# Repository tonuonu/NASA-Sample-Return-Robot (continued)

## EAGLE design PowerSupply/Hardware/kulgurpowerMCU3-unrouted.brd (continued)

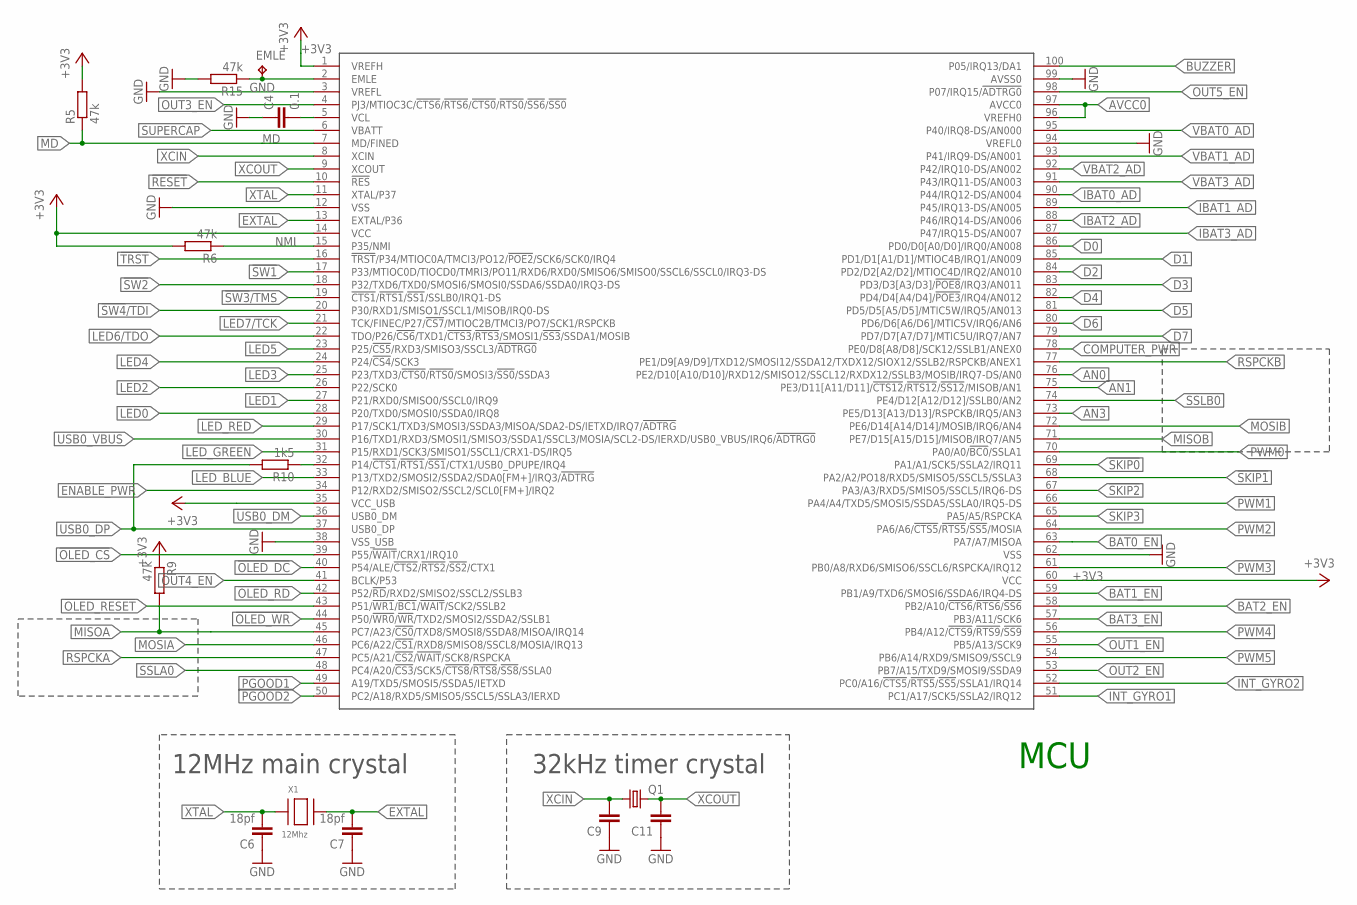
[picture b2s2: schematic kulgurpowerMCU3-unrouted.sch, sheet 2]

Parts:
C4: 0.1; 0603-CAP
C6, C7: 18pf; 0603-CAP
C9, C11: CAP0603-CAP; 0603-CAP
EMLE: TPB1,27; B1,27
Q1: CRYSTALMM20SS; MM20SS
R5, R6, R9, R15: 47k; R0603
R10: 1k5; R0603
U$14: R5F5630ADDFP; LTQFP100
X1: 12Mhz; NX5032

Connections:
!OLED_CS: U$14.39 (P55/!WAIT!/CRX1/IRQ10); also elsewhere on the board
!OLED_DC: U$14.40 (P54/ALE/!CTS2!/!RTS2!/!SS2!/CTX1); also elsewhere on the board
!OLED_RD: U$14.42 (P52/!RD!/RXD2/SMISO2/SSCL2/SSLB3); also elsewhere on the board
!OLED_RESET: U$14.43 (P51/!WR1!/!BC1!/!WAIT!/SCK2/SSLB2); also elsewhere on the board
!OLED_WR: U$14.44 (P50/!WR0!/!WR!/TXD2/SMOSI2/SSDA2/SSLB1); also elsewhere on the board
!RESET: U$14.10 (!RES!); also elsewhere on the board
!SKIP0: U$14.69 (PA1/A1/SCK5/SSLA2/IRQ11); also elsewhere on the board
!SKIP1: U$14.68 (PA2/A2/PO18/RXD5/SMISO5/SSCL5/SSLA3); also elsewhere on the board
!SKIP2: U$14.67 (PA3/A3/RXD5/SMISO5/SSCL5/IRQ6-DS); also elsewhere on the board
!SKIP3: U$14.65 (PA5/A5/RSPCKA); also elsewhere on the board
!SW1: U$14.17 (P33/MTIOC0D/TIOCD0/TMRI3/PO11/RXD6/RXD0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); also elsewhere on the board
!SW2: U$14.18 (P32/TXD6/TXD0/SMOSI6/SMOSI0/SSDA6/SSDA0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); also elsewhere on the board
!SW3!/TMS: U$14.19 (!CTS1!/!RTS1!/!SS1!/SSLB0/IRQ1-DS); also elsewhere on the board
!SW4!/TDI: U$14.20 (P30/RXD1/SMISO1/SSCL1/MISOB/IRQ0-DS); also elsewhere on the board
!TRST: U$14.16 (!TRST!/P34/MTIOC0A/TMCI3/PO12/!POE2!/SC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); also elsewhere on the board
+3V3: R5.2, R6.2, R9.1, U$14.1 (VREFH), U$14.14 (VCC), U$14.35 (VCC_USB), U$14.60 (VCC); also elsewhere on the board
AN0: U$14.76 (PE2/D10[A10/D10]/RXD12/SMISO12/SSCL12/R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); also elsewhere on the board
AN1: U$14.75 (PE3/D11[A11/D11]/!CTS12!/!RTS12!/!SS12!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); also elsewhere on the board
AN3: U$14.73 (PE5/D13[A13/D13]/RSPCKB/IRQ5/AN3); also elsewhere on the board
AVCC0: U$14.96 (VREFH0), U$14.97 (AVCC0); also elsewhere on the board
BAT0_EN: U$14.63 (PA7/A7/MISOA); also elsewhere on the board
BAT1_EN: U$14.59 (PB1/A9/TXD6/SMOSI6/SSDA6/IRQ4-DS); also elsewhere on the board
BAT2_EN: U$14.58 (PB2/A10/!CTS6!/!RTS6!/!SS6!); also elsewhere on the board
BAT3_EN: U$14.57 (PB3/A11/SCK6); also elsewhere on the board
BUZZER: U$14.100 (P05/IRQ13/DA1); also elsewhere on the board
COMPUTER_PWR: U$14.78 (PE0/D8[A8/D8]/SCK12/SSLB1/ANEX0); also elsewhere on the board
D0: U$14.86 (PD0/D0[A0/D0]/IRQ0/AN008); also elsewhere on the board
D1: U$14.85 (PD1/D1[A1/D1]/MTIOC4B/IRQ1/AN009); also elsewhere on the board
D2: U$14.84 (PD2/D2[A2/D2]/MTIOC4D/IRQ2/AN010); also elsewhere on the board
D3: U$14.83 (PD3/D3[A3/D3]/!POE8!/IRQ3/AN011); also elsewhere on the board
D4: U$14.82 (PD4/D4[A4/D4]/!POE3!/IRQ4/AN012); also elsewhere on the board
D5: U$14.81 (PD5/D5[A5/D5]/MTIC5W/IRQ5/AN013); also elsewhere on the board
D6: U$14.80 (PD6/D6[A6/D6]/MTIC5V/IRQ6/AN6); also elsewhere on the board
D7: U$14.79 (PD7/D7[A7/D7]/MTIC5U/IRQ7/AN7); also elsewhere on the board
EMLE: EMLE.TP, R15.1, U$14.2 (EMLE); also elsewhere on the board
ENABLE_PWR: U$14.34 (P12/RXD2/SMISO2/SSCL2/SCL0[FM+]/IRQ2); also elsewhere on the board
EXTAL: C7.2, U$14.13 (EXTAL/P36), X1.P$2
GND: C4.1, C6.1, C7.1, C9.1, C11.1, R15.2, U$14.3 (VREFL), U$14.12 (VSS), U$14.38 (VSS_USB), U$14.62 (VSS), U$14.94 (VREFL0), U$14.99 (AVSS0); also elsewhere on the board
IBAT0_AD: U$14.90 (P44/IRQ12-DS/AN004); also elsewhere on the board
IBAT1_AD: U$14.89 (P45/IRQ13-DS/AN005); also elsewhere on the board
IBAT2_AD: U$14.88 (P46/IRQ14-DS/AN006); also elsewhere on the board
IBAT3_AD: U$14.87 (P47/IRQ15-DS/AN007); also elsewhere on the board
INT_GYRO1: U$14.51 (PC1/A17/SCK5/SSLA2/IRQ12); also elsewhere on the board
INT_GYRO2: U$14.52 (PC0/A16/!CTS5!/!RTS5!/!SS5!/SSLA1/IRQ14); also elsewhere on the board
LED0: U$14.28 (P20/TXD0/SMOSI0/SSDA0/IRQ8); also elsewhere on the board
LED1: U$14.27 (P21/RXD0/SMISO0/SSCL0/IRQ9); also elsewhere on the board
LED2: U$14.26 (P22/SCK0); also elsewhere on the board
LED3: U$14.25 (P23/TXD3/!CTS0!/!RTS0!/SMOSI3/!SS0!/SSD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); also elsewhere on the board
LED4: U$14.24 (P24/!CS4!/SCK3); also elsewhere on the board
LED5: U$14.23 (P25/!CS5!/RXD3/SMISO3/SSCL3/!ADTRG0!); also elsewhere on the board
LED6/TDO: U$14.22 (TDO/P26/!CS6!/TXD1/!CTS3!/!RTS3!/SMOSI1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); also elsewhere on the board
LED7/TCK: U$14.21 (TCK/FINEC/P27/!CS7!/MTIOC2B/TMCI3/PO7/S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); also elsewhere on the board
LED_BLUE: U$14.33 (P13/TXD2/SMOSI2/SSDA2/SDA0[FM+]/IRQ3/!A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); also elsewhere on the board
LED_GREEN: U$14.31 (P15/RXD1/SCK3/SMISO1/SSCL1/CRX1-DS/IRQ5); also elsewhere on the board
LED_RED: U$14.29 (P17/SCK1/TXD3/SMOSI3/SSDA3/MISOA/SDA2-D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); also elsewhere on the board
MD: R5.1, U$14.7 (MD/FINED); also elsewhere on the board
MISOA: R9.2, U$14.45 (PC7/A23/!CS0!/TXD8/SMOSI8/SSDA8/MISOA/I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); also elsewhere on the board
MISOB: U$14.71 (PE7/D15[A15/D15]/MISOB/IRQ7/AN5); also elsewhere on the board
MOSIA: U$14.46 (PC6/A22/!CS1!/RXD8/SMISO8/SSCL8/MOSIA/I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); also elsewhere on the board
MOSIB: U$14.72 (PE6/D14[A14/D14]/MOSIB/IRQ6/AN4); also elsewhere on the board
unnamed: C4.2, U$14.5 (VCL)
NMI: R6.1, U$14.15 (P35/NMI)
OUT1_EN: U$14.55 (PB5/A13/SCK9); also elsewhere on the board
OUT2_EN: U$14.53 (PB7/A15/TXD9/SMOSI9/SSDA9); also elsewhere on the board
OUT3_EN: U$14.4 (PJ3/MTIOC3C/!CTS6!/!RTS6!/!CTS0!/!RTS0!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); also elsewhere on the board
OUT4_EN: U$14.41 (BCLK/P53); also elsewhere on the board
OUT5_EN: U$14.98 (P07/IRQ15/!ADTRG0); also elsewhere on the board
PGOOD1: U$14.49 (A19/TXD5/SMOSI5/SSDA5/IETXD); also elsewhere on the board
PGOOD2: U$14.50 (PC2/A18/RXD5/SMISO5/SSCL5/SSLA3/IERXD); also elsewhere on the board
PWM0: U$14.70 (PA0/A0/!BC0!/SSLA1); also elsewhere on the board
PWM1: U$14.66 (PA4/A4/TXD5/SMOSI5/SSDA5/SSLA0/IRQ5-DS); also elsewhere on the board
PWM2: U$14.64 (PA6/A6/!CTS5!/!RTS5!/!SS5!/MOSIA); also elsewhere on the board
PWM3: U$14.61 (PB0/A8/RXD6/SMISO6/SSCL6/RSPCKA/IRQ12); also elsewhere on the board
PWM4: U$14.56 (PB4/A12/!CTS9!/!RTS9!/!SS9!); also elsewhere on the board
PWM5: U$14.54 (PB6/A14/RXD9/SMISO9/SSCL9); also elsewhere on the board
RSPCKA: U$14.47 (PC5/A21/!CS2!/!WAIT!/SCK8/RSPCKA); also elsewhere on the board
RSPCKB: U$14.77 (PE1/D9[A9/D9]/TXD12/SMOSI12/SSDA12/TXDX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); also elsewhere on the board
SSLA0: U$14.48 (PC4/A20/!CS3!/SCK5/!CTS8!/!RTS8!/!SS8!/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); also elsewhere on the board
SSLB0: U$14.74 (PE4/D12[A12/D12]/SSLB0/AN2); also elsewhere on the board
SUPERCAP: U$14.6 (VBATT); also elsewhere on the board
USB0_DM: U$14.36 (USB0_DM); also elsewhere on the board
USB0_DP: R10.2, U$14.37 (USB0_DP); also elsewhere on the board
USB0_DPUPE: R10.1, U$14.32 (P14/!CTS1!/!RTS1!/!SS1!/CTX1/USB0_DPUPE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)
USB0_VBUS: U$14.30 (P16/TXD1/RXD3/SMOSI1/SMISO3/SSDA1/SSCL3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); also elsewhere on the board
VBAT0_AD: U$14.95 (P40/IRQ8-DS/AN000); also elsewhere on the board
VBAT1_AD: U$14.93 (P41/IRQ9-DS/AN001); also elsewhere on the board
VBAT2_AD: U$14.92 (P42/IRQ10-DS/AN002); also elsewhere on the board
VBAT3_AD: U$14.91 (P43/IRQ11-DS/AN003); also elsewhere on the board
XCIN: C9.2, Q1.1, U$14.8 (XCIN)
XCOUT: C11.2, Q1.4 (2), U$14.9 (XCOUT)
XTAL: C6.2, U$14.11 (XTAL/P37), X1.P$1

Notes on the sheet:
MCU
32kHz timer crystal
12MHz main crystal

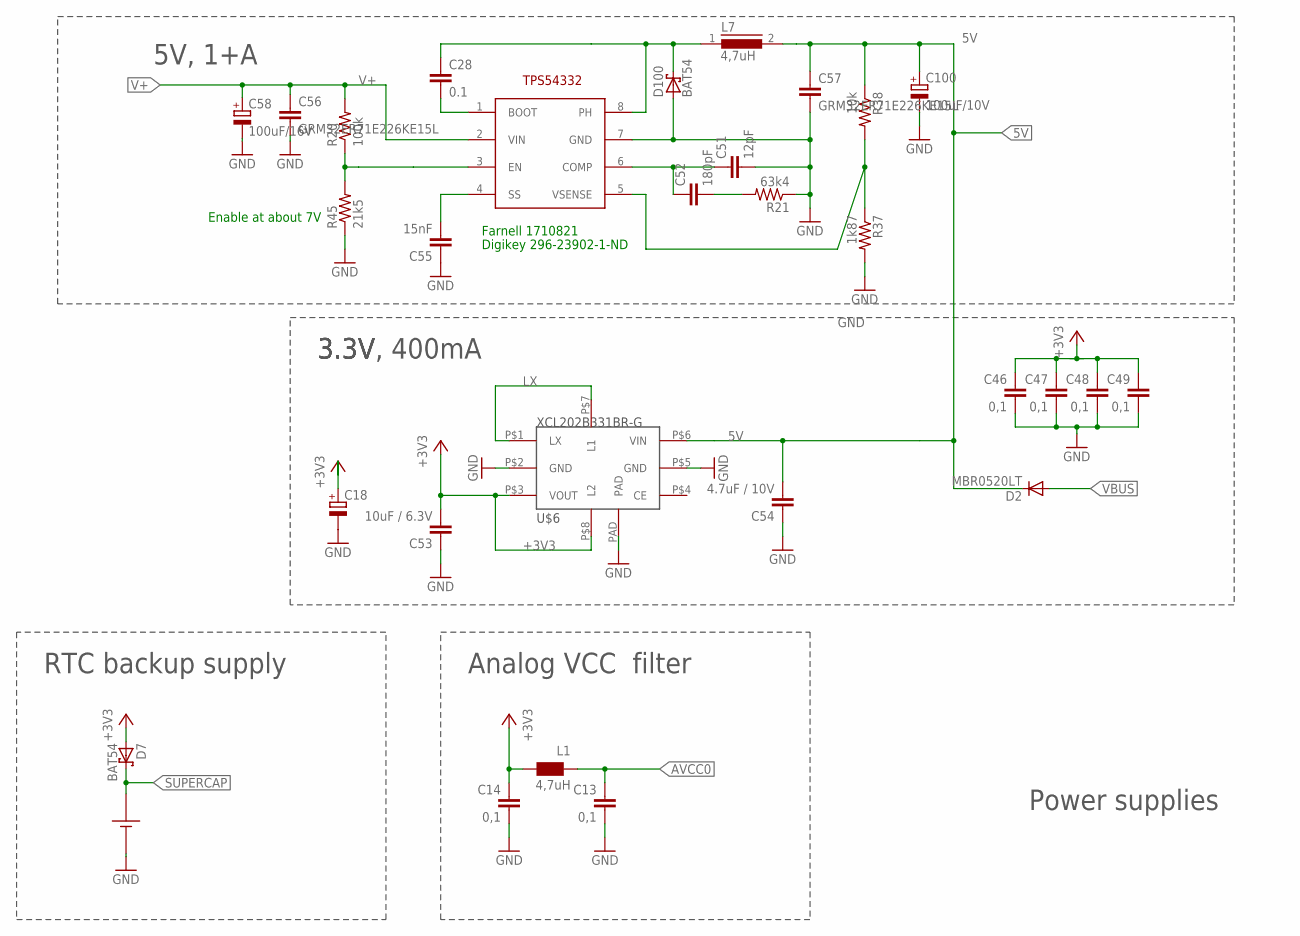
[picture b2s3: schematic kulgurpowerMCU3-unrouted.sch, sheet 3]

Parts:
C13, C14, C46, C47, C48, C49: 0,1; 0603-CAP
C18: CPOL-EUC/6032-28R; C/6032-28R
C28: 0.1; 0603-CAP
C51: 12pF; 0603-CAP
C52: 180pF; 0603-CAP
C53: 10uF / 6.3V; C0603
C54: 4.7uF / 10V; C0603
C55: 15nF; 0603-CAP
C56, C57: GRM32ER71E226KE15L; C1210
C58: 100uF/16V; C/6032-28R
C100: 100uF/10V; C/6032-28R
D2: MBR0520LT; SOD123
D7, D100: BAT54; SOT23
L1: 4,7uH; WE-KI_0805_B
L7: 4,7uH; DR73
R20: 100k; 0603-RES
R21: 63k4; 0603-RES
R37: 1k87; 0603-RES
R38: 10k; 0603-RES
R45: 21k5; 0603-RES
U$1: EDLRD224V3R6C
U$5: TPS54332; SO8
U$6: XCL202B331BR-G; CL2025

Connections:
5V: C54.2, C57.1, C100.+, D2.C, L7.2, R38.1, U$6.P$6 (VIN); also elsewhere on the board
+3V3: C14.1, C18.+, C46.1, C47.1, C48.1, C49.1, C53.2, D7.1 (A), L1.1 (2), U$6.P$3 (VOUT), U$6.P$8 (L2); also elsewhere on the board
AVCC0: C13.1, L1.2 (1); also elsewhere on the board
ENABLE_PANDA: R20.1, R45.2, U$5.3 (EN)
GND: C13.2, C14.2, C18.-, C46.2, C47.2, C48.2, C49.2, C51.2, C53.1, C54.1, C55.1, C56.2, C57.2, C58.-, C100.-, D100.1 (A), R21.1, R37.2, R45.1, U$1.N, U$5.7 (GND), U$6.P$2 (GND), U$6.P$5 (GND), U$6.PAD; also elsewhere on the board
LX: U$6.P$1 (LX), U$6.P$7 (L1)
unnamed: C55.2, U$5.4 (SS)
unnamed: C51.1, C52.1, U$5.6 (COMP)
unnamed: C52.2, R21.2
unnamed: C28.2, U$5.1 (BOOT)
unnamed: R37.1, R38.2, U$5.5 (VSENSE)
unnamed: C28.1, D100.3 (C), L7.1, U$5.8 (PH)
SUPERCAP: D7.3 (C), U$1.P; also elsewhere on the board
V+: C56.1, C58.+, R20.2, U$5.2 (VIN); also elsewhere on the board
VBUS: D2.A; also elsewhere on the board

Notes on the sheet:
Power supplies
3.3V
3.3V, 400mA
5V, 1+A
RTC backup supply
Analog VCC filter
Farnell 1710821
Digikey 296-23902-1-ND
Enable at about 7V

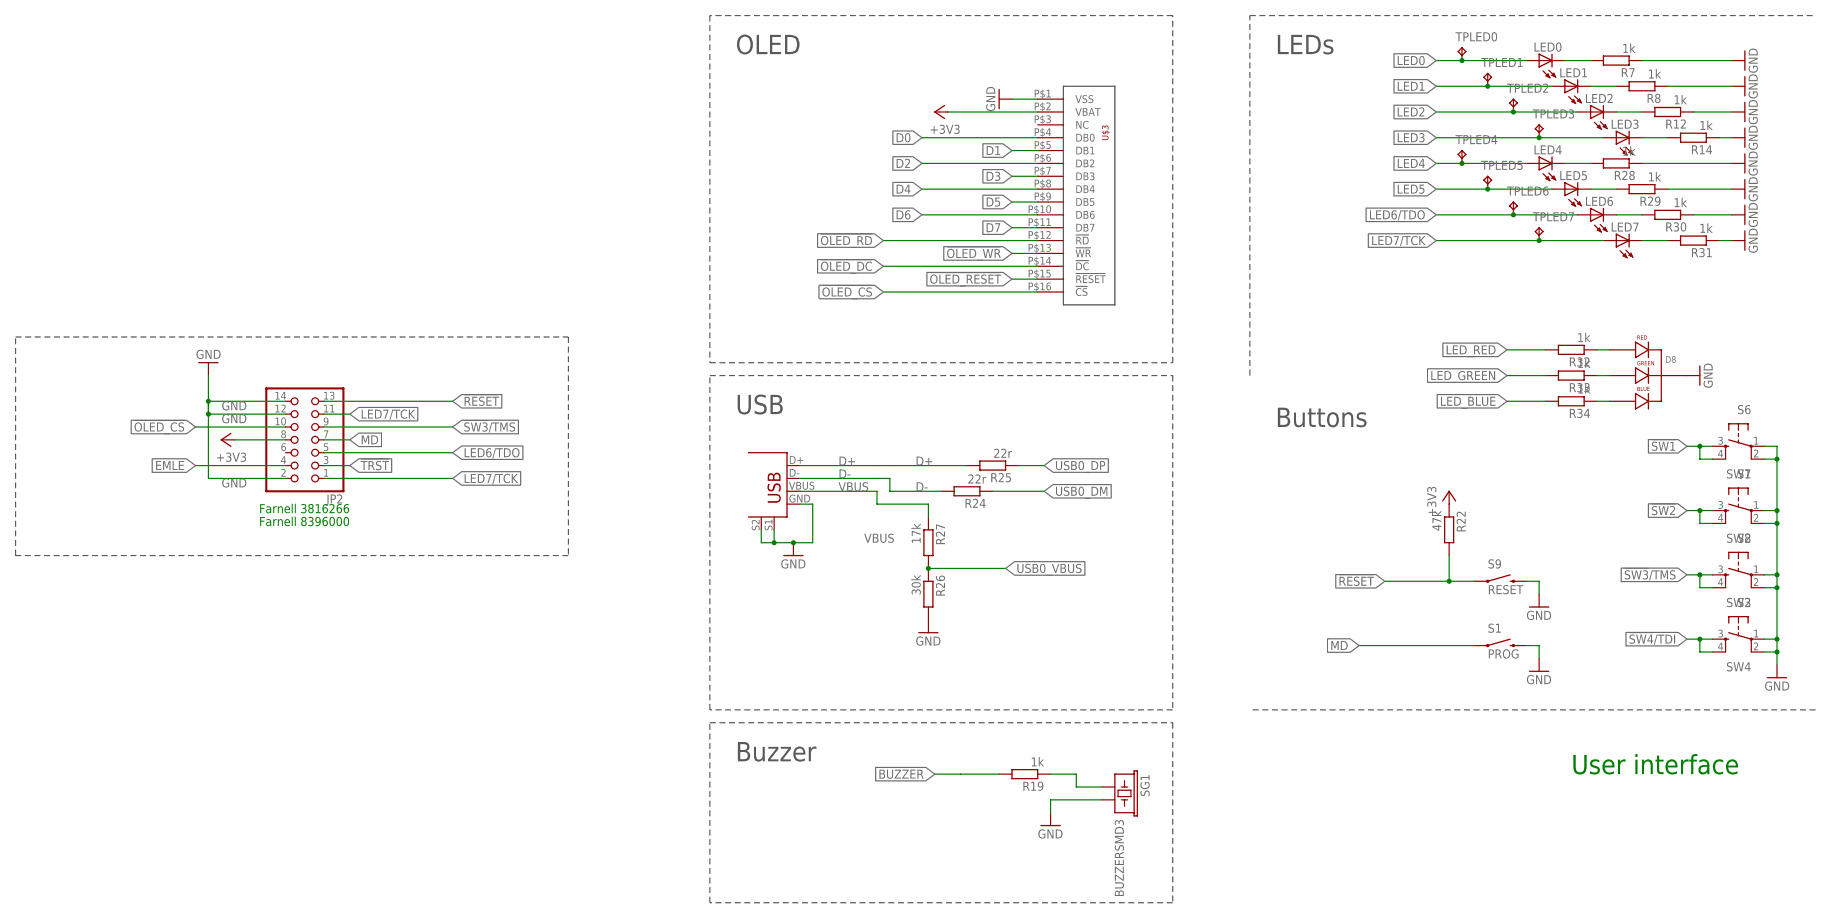
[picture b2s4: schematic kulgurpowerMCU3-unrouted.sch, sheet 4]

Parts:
D8: WP154A4SUREQBFZGW; LED-RGB-THRU
JP2: PINHD-2X7; 2X07
LED0, LED1, LED2, LED3, LED4, LED5, LED6, LED7: LED0603; LED-0603
R7, R8, R12, R14, R19, R28, R29, R30, R31, R32, R33, R34: 1k; R0603
R22: 47k; R0603
R24, R25: 22r; R0603
R26: 30k; R0603
R27: 17k; R0603
S1: PROG; TACTILE-PTH-SIDEEZ
S2: SW4; TACTILE-PTH
S6: SW1; TACTILE-PTH
S7: SW2; TACTILE-PTH
S8: SW3; TACTILE-PTH
S9: RESET; TACTILE-PTH-SIDEEZ
SG1: BUZZERSMD3; BUZZER-CMT1102
TPLED0, TPLED1, TPLED2, TPLED3, TPLED4, TPLED5, TPLED6, TPLED7: LED0; B1,27
U$2: USB+SHIELD; USB-B-PTH
U$3: ER-OLEDM032-1

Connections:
!OLED_CS: JP2.10, U$3.P$16 (!CS); also elsewhere on the board
!OLED_DC: U$3.P$14 (!DC); also elsewhere on the board
!OLED_RD: U$3.P$12 (!RD); also elsewhere on the board
!OLED_RESET: U$3.P$15 (!RESET); also elsewhere on the board
!OLED_WR: U$3.P$13 (!WR); also elsewhere on the board
!RESET: JP2.13, R22.2, S9.1; also elsewhere on the board
!SW1: S6.3, S6.4; also elsewhere on the board
!SW2: S7.3, S7.4; also elsewhere on the board
!SW3!/TMS: JP2.9, S8.3, S8.4; also elsewhere on the board
!SW4!/TDI: S2.3, S2.4; also elsewhere on the board
!TRST: JP2.3; also elsewhere on the board
+3V3: JP2.8, R22.1, U$3.P$2 (VBAT); also elsewhere on the board
BUZZER: R19.2; also elsewhere on the board
BUZZER_X: R19.1, SG1.1
D0: U$3.P$4 (DB0); also elsewhere on the board
D1: U$3.P$5 (DB1); also elsewhere on the board
D2: U$3.P$6 (DB2); also elsewhere on the board
D3: U$3.P$7 (DB3); also elsewhere on the board
D4: U$3.P$8 (DB4); also elsewhere on the board
D5: U$3.P$9 (DB5); also elsewhere on the board
D6: U$3.P$10 (DB6); also elsewhere on the board
D7: U$3.P$11 (DB7); also elsewhere on the board
D+: R25.2, U$2.D+
D-: R24.2, U$2.D-
EMLE: JP2.4; also elsewhere on the board
GND: D8.2 (CATHODE), JP2.2, JP2.12, JP2.14, R7.1, R8.1, R12.1, R14.1, R26.2, R28.1, R29.1, R30.1, R31.1, S1.2, S2.1, S2.2, S6.1, S6.2, S7.1, S7.2, S8.1, S8.2, S9.2, SG1.2, U$2.GND, U$2.S1, U$2.S2, U$3.P$1 (VSS); also elsewhere on the board
LED0: LED0.A, TPLED0.TP; also elsewhere on the board
LED1: LED1.A, TPLED1.TP; also elsewhere on the board
LED2: LED2.A, TPLED2.TP; also elsewhere on the board
LED3: LED3.A, TPLED3.TP; also elsewhere on the board
LED4: LED4.A, TPLED4.TP; also elsewhere on the board
LED5: LED5.A, TPLED5.TP; also elsewhere on the board
LED6/TDO: JP2.5, LED6.A, TPLED6.TP; also elsewhere on the board
LED7/TCK: JP2.1, JP2.11, LED7.A, TPLED7.TP; also elsewhere on the board
LED_BLUE: R34.2; also elsewhere on the board
LED_GREEN: R33.2; also elsewhere on the board
LED_RED: R32.2; also elsewhere on the board
MD: JP2.7, S1.1; also elsewhere on the board
unnamed: LED0.C, R7.2
unnamed: D8.1 (RED_CATHODE), R32.1
unnamed: LED1.C, R8.2
unnamed: LED2.C, R12.2
unnamed: LED3.C, R14.2
unnamed: LED4.C, R28.2
unnamed: LED5.C, R29.2
unnamed: LED6.C, R30.2
unnamed: LED7.C, R31.2
unnamed: D8.3 (GREEN_CATHODE), R33.1
unnamed: D8.4 (BLUE_CATHODE), R34.1
USB0_DM: R24.1; also elsewhere on the board
USB0_DP: R25.1; also elsewhere on the board
USB0_VBUS: R26.1, R27.2; also elsewhere on the board
VBUS: R27.1, U$2.VBUS; also elsewhere on the board

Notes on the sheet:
User interface
Farnell 8396000
Farnell 3816266
OLED
LEDs
Buttons
USB
Buzzer

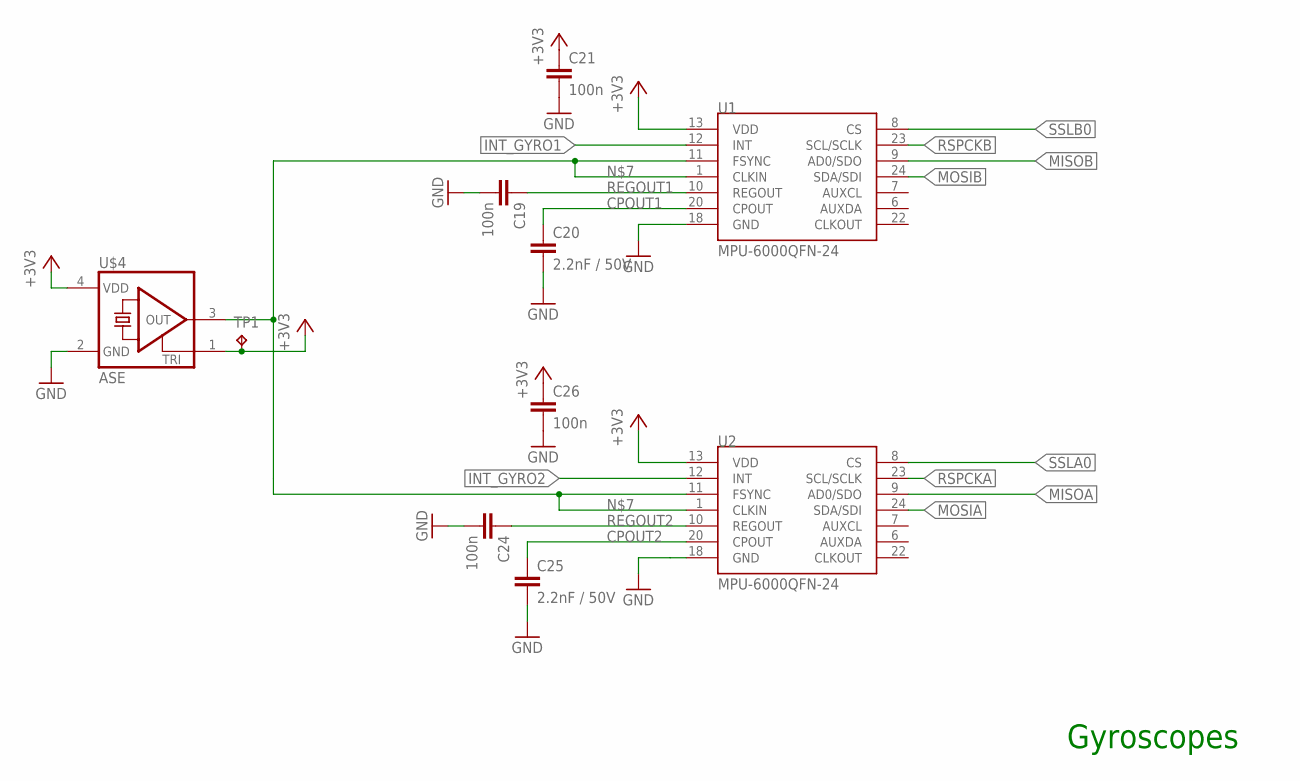
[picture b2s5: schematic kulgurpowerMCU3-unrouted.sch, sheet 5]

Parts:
C19, C21, C24, C26: 100n; C0603
C20, C25: 2.2nF / 50V; C0402
TP1: TPB1,27; B1,27
U1, U2: MPU-6000QFN-24; QFN-24-TESTING
U$4: ASE

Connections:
+3V3: C21.1, C26.1, TP1.TP, U1.13 (VDD), U2.13 (VDD), U$4.1 (TRI), U$4.4 (VDD); also elsewhere on the board
CPOUT1: C20.1, U1.20 (CPOUT)
CPOUT2: C25.1, U2.20 (CPOUT)
GND: C19.2, C20.2, C21.2, C24.2, C25.2, C26.2, U1.18 (GND), U2.18 (GND), U$4.2 (GND); also elsewhere on the board
INT_GYRO1: U1.12 (INT); also elsewhere on the board
INT_GYRO2: U2.12 (INT); also elsewhere on the board
MISOA: U2.9 (AD0/SDO); also elsewhere on the board
MISOB: U1.9 (AD0/SDO); also elsewhere on the board
MOSIA: U2.24 (SDA/SDI); also elsewhere on the board
MOSIB: U1.24 (SDA/SDI); also elsewhere on the board
unnamed: U1.1 (CLKIN), U1.11 (FSYNC), U2.1 (CLKIN), U2.11 (FSYNC), U$4.3 (OUT)
REGOUT1: C19.1, U1.10 (REGOUT)
REGOUT2: C24.1, U2.10 (REGOUT)
RSPCKA: U2.23 (SCL/SCLK); also elsewhere on the board
RSPCKB: U1.23 (SCL/SCLK); also elsewhere on the board
SSLA0: U2.8 (CS); also elsewhere on the board
SSLB0: U1.8 (CS); also elsewhere on the board

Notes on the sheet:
Gyroscopes

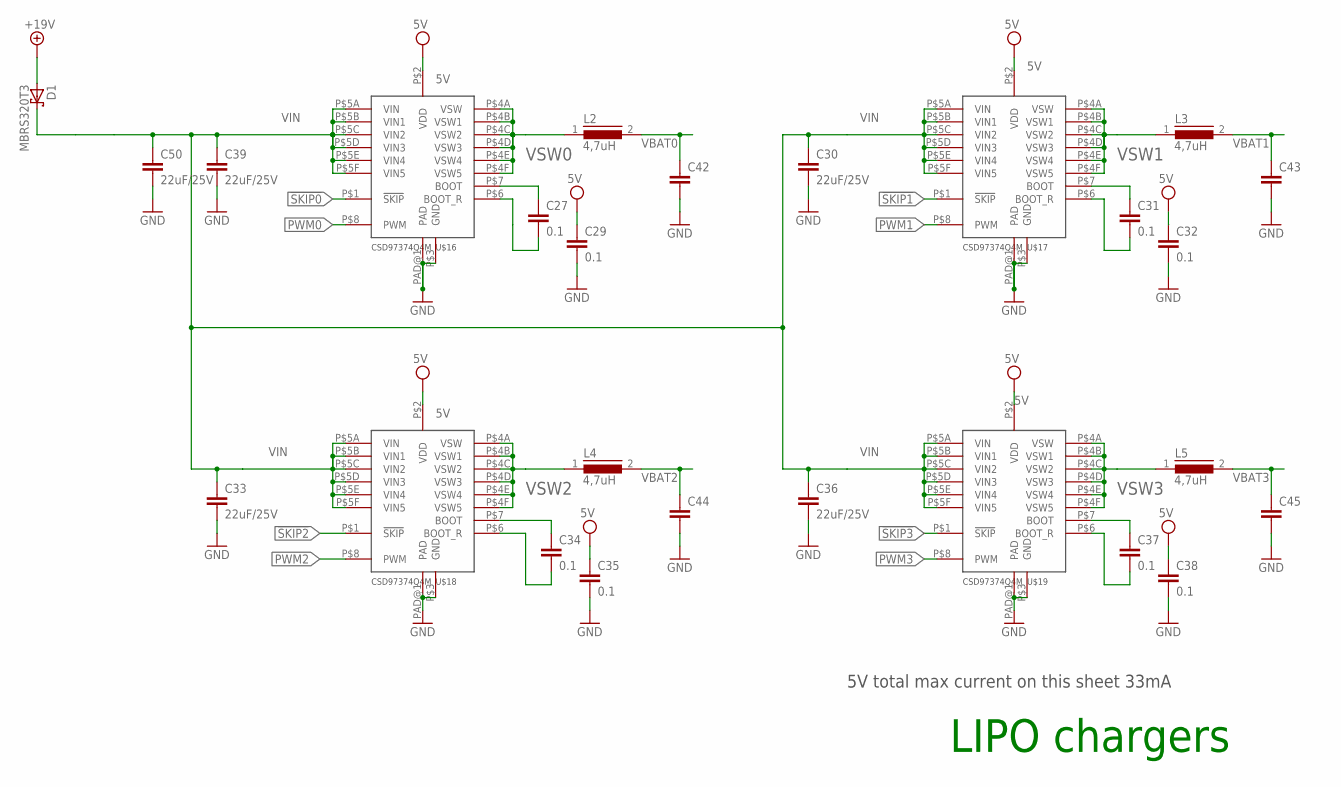
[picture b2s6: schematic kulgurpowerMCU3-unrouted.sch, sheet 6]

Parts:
C27, C29, C31, C32, C34, C35, C37, C38: 0.1; C0603
C30, C33, C36, C39, C50: 22uF/25V; C1210
C42, C43, C44, C45: C-EUC1210; C1210
D1: MBRS320T3; SMC
L2, L3, L4, L5: 4,7uH; DR73
U$16, U$17, U$18, U$19: CSD97374Q4M

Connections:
5V: C29.1, C32.1, C35.1, C38.1, U$16.P$2 (VDD), U$17.P$2 (VDD), U$18.P$2 (VDD), U$19.P$2 (VDD); also elsewhere on the board
!SKIP0: U$16.P$1 (!SKIP); also elsewhere on the board
!SKIP1: U$17.P$1 (!SKIP); also elsewhere on the board
!SKIP2: U$18.P$1 (!SKIP); also elsewhere on the board
!SKIP3: U$19.P$1 (!SKIP); also elsewhere on the board
+19V: D1.A; also elsewhere on the board
GND: C29.2, C30.2, C32.2, C33.2, C35.2, C36.2, C38.2, C39.2, C42.2, C43.2, C44.2, C45.2, C50.2, U$16.P$3 (GND), U$16.PAD@1 (PAD), U$17.P$3 (GND), U$17.PAD@1 (PAD), U$18.P$3 (GND), U$18.PAD@1 (PAD), U$19.P$3 (GND), U$19.PAD@1 (PAD); also elsewhere on the board
unnamed: C37.1, U$19.P$7 (BOOT)
unnamed: C31.1, U$17.P$7 (BOOT)
unnamed: C37.2, U$19.P$6 (BOOT_R)
unnamed: C31.2, U$17.P$6 (BOOT_R)
unnamed: C27.1, U$16.P$7 (BOOT)
unnamed: C27.2, U$16.P$6 (BOOT_R)
unnamed: C34.1, U$18.P$7 (BOOT)
unnamed: C34.2, U$18.P$6 (BOOT_R)
PWM0: U$16.P$8 (PWM); also elsewhere on the board
PWM1: U$17.P$8 (PWM); also elsewhere on the board
PWM2: U$18.P$8 (PWM); also elsewhere on the board
PWM3: U$19.P$8 (PWM); also elsewhere on the board
VBAT0: C42.1, L2.2; also elsewhere on the board
VBAT1: C43.1, L3.2; also elsewhere on the board
VBAT2: C44.1, L4.2; also elsewhere on the board
VBAT3: C45.1, L5.2; also elsewhere on the board
VIN: C30.1, C33.1, C36.1, C39.1, C50.1, D1.C, U$16.P$5A (VIN), U$16.P$5B (VIN1), U$16.P$5C (VIN2), U$16.P$5D (VIN3), U$16.P$5E (VIN4), U$16.P$5F (VIN5), U$17.P$5A (VIN), U$17.P$5B (VIN1), U$17.P$5C (VIN2), U$17.P$5D (VIN3), U$17.P$5E (VIN4), U$17.P$5F (VIN5), U$18.P$5A (VIN), U$18.P$5B (VIN1), U$18.P$5C (VIN2), U$18.P$5D (VIN3), U$18.P$5E (VIN4), U$18.P$5F (VIN5), U$19.P$5A (VIN), U$19.P$5B (VIN1), U$19.P$5C (VIN2), U$19.P$5D (VIN3), U$19.P$5E (VIN4), U$19.P$5F (VIN5)
VSW0: L2.1, U$16.P$4A (VSW), U$16.P$4B (VSW1), U$16.P$4C (VSW2), U$16.P$4D (VSW3), U$16.P$4E (VSW4), U$16.P$4F (VSW5)
VSW1: L3.1, U$17.P$4A (VSW), U$17.P$4B (VSW1), U$17.P$4C (VSW2), U$17.P$4D (VSW3), U$17.P$4E (VSW4), U$17.P$4F (VSW5)
VSW2: L4.1, U$18.P$4A (VSW), U$18.P$4B (VSW1), U$18.P$4C (VSW2), U$18.P$4D (VSW3), U$18.P$4E (VSW4), U$18.P$4F (VSW5)
VSW3: L5.1, U$19.P$4A (VSW), U$19.P$4B (VSW1), U$19.P$4C (VSW2), U$19.P$4D (VSW3), U$19.P$4E (VSW4), U$19.P$4F (VSW5)

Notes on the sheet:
LIPO chargers
5V total max current on this sheet 33mA

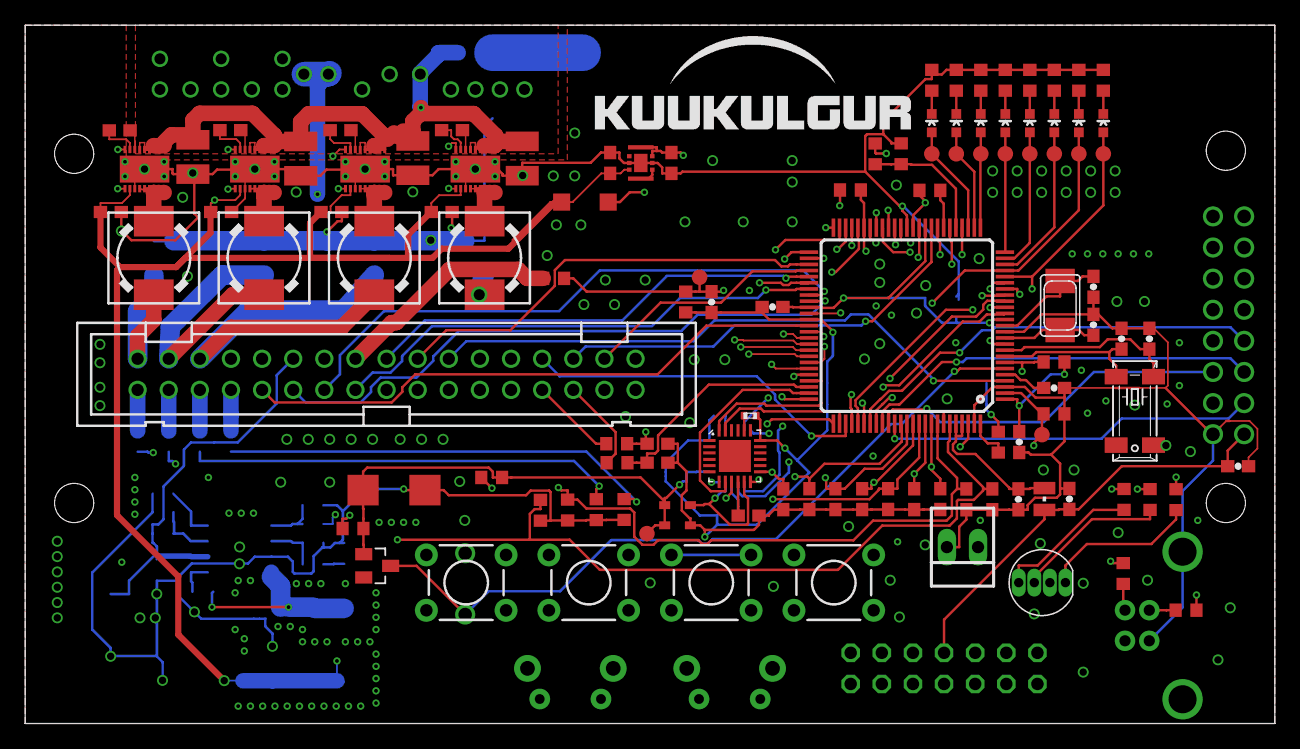
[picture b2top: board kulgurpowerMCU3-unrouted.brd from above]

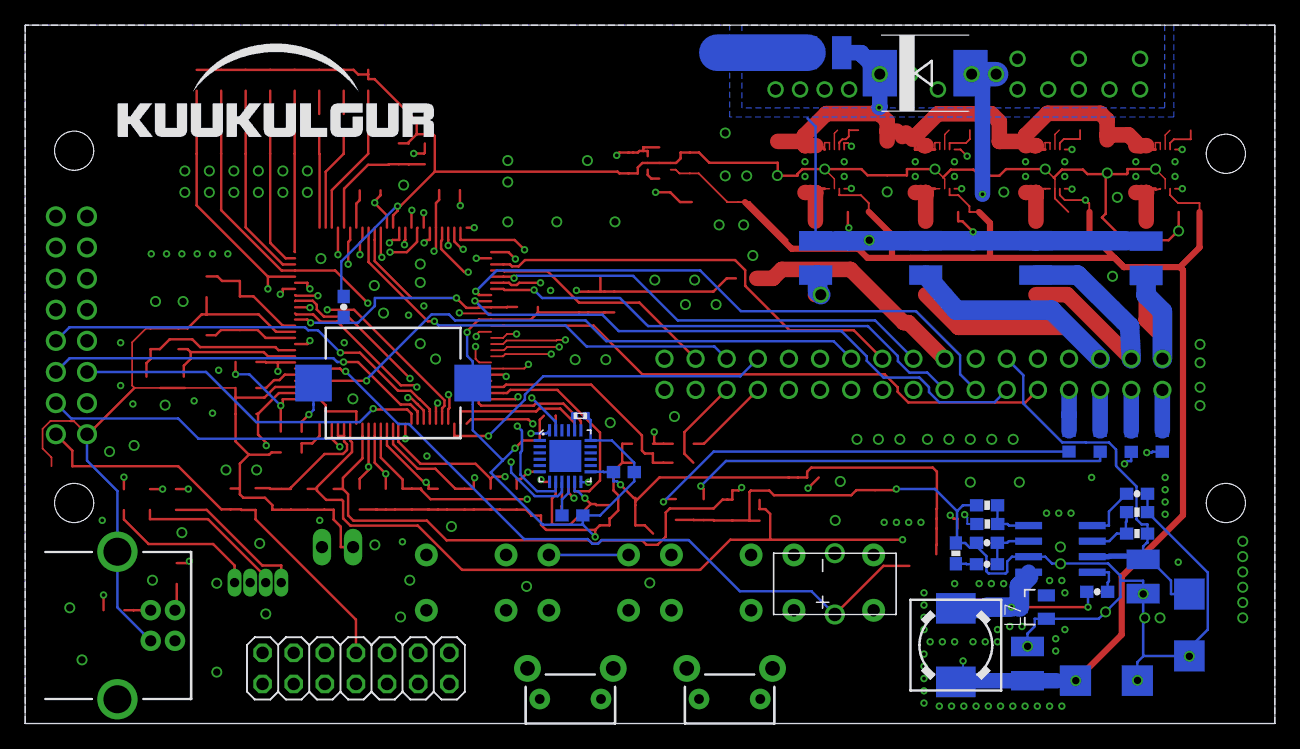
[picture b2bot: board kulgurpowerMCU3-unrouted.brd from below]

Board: 4 copper layers, 102.0 x 57.0 mm, 150 parts (37 on the bottom side), 141 nets.

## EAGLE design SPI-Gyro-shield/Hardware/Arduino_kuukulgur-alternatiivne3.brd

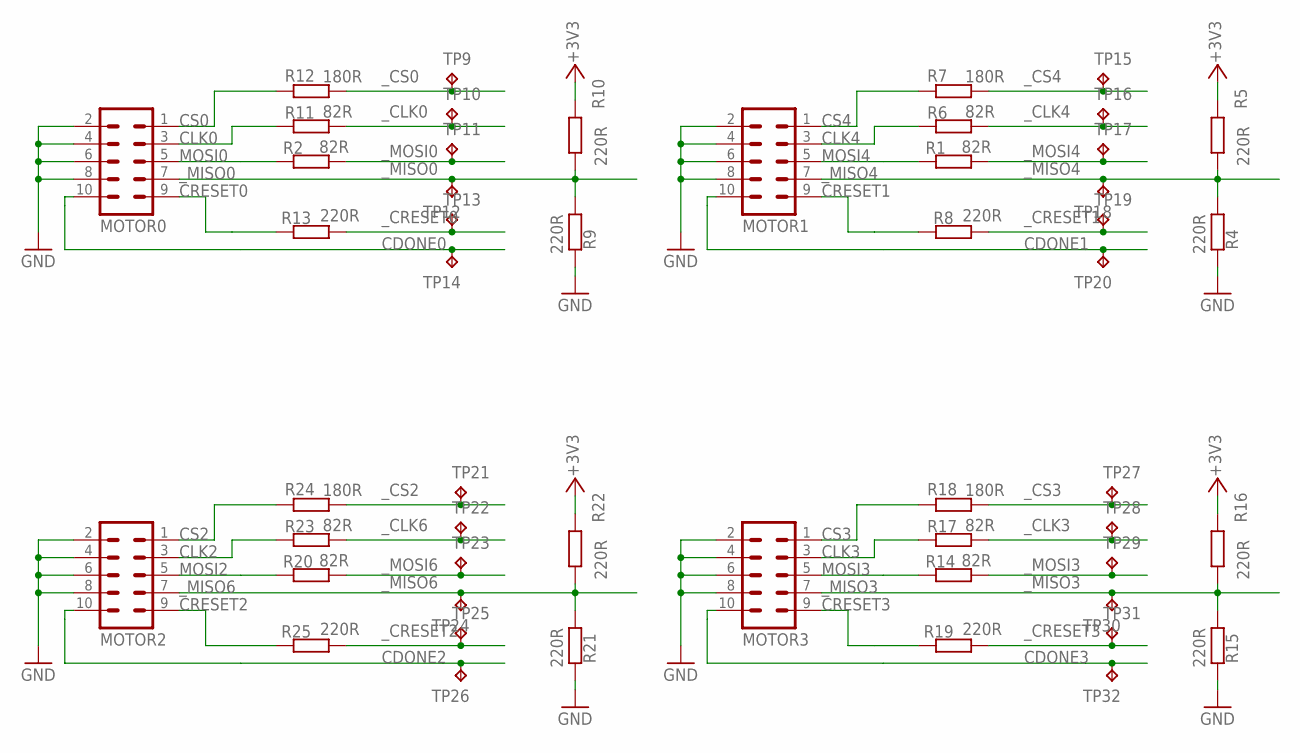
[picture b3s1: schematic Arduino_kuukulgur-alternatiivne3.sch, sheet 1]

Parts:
MOTOR0, MOTOR1, MOTOR2, MOTOR3: MA05-2
R1, R2, R6, R11, R14, R17, R20, R23: 82R; R0603-ROUND
R4, R5, R8, R9, R10, R13, R15, R16, R19, R21, R22, R25: 220R; R0603-ROUND
R7, R12, R18, R24: 180R; R0603-ROUND
TP9, TP10, TP11, TP12, TP13, TP14, TP15, TP16, TP17, TP18, TP19, TP20, TP21, TP22, TP23, TP24, TP25, TP26, TP27, TP28, TP29, TP30, TP31, TP32: TPB1,27; B1,27

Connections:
+4V5: R5.1, R10.1, R16.1, R22.1; also elsewhere on the board
CDONE0: MOTOR0.10, TP14.TP; also elsewhere on the board
CDONE1: MOTOR1.10, TP20.TP; also elsewhere on the board
CDONE2: MOTOR2.10, TP26.TP; also elsewhere on the board
CDONE3: MOTOR3.10, TP32.TP; also elsewhere on the board
CLK0: MOTOR0.3, R11.2
CLK2: MOTOR2.3, R23.2
CLK3: MOTOR3.3, R17.2
CLK4: MOTOR1.3, R6.2
CRESET0: MOTOR0.9, R13.1
CRESET1: MOTOR1.9, R8.1
CRESET2: MOTOR2.9, R25.1
CRESET3: MOTOR3.9, R19.1
CS0: MOTOR0.1, R12.2
CS2: MOTOR2.1, R24.2
CS3: MOTOR3.1, R18.2
CS4: MOTOR1.1, R7.2
GND: MOTOR0.2, MOTOR0.4, MOTOR0.6, MOTOR0.8, MOTOR1.2, MOTOR1.4, MOTOR1.6, MOTOR1.8, MOTOR2.2, MOTOR2.4, MOTOR2.6, MOTOR2.8, MOTOR3.2, MOTOR3.4, MOTOR3.6, MOTOR3.8, R4.2, R9.2, R15.2, R21.2; also elsewhere on the board
MOSI0: MOTOR0.5, R2.2
MOSI2: MOTOR2.5, R20.2
MOSI3: MOTOR3.5, R14.2
MOSI4: MOTOR1.5, R1.2
_CLK0: R11.1, TP10.TP; also elsewhere on the board
_CLK3: R17.1, TP28.TP; also elsewhere on the board
_CLK4: R6.1, TP16.TP; also elsewhere on the board
_CLK6: R23.1, TP22.TP; also elsewhere on the board
_CRESET0: R13.2, TP13.TP; also elsewhere on the board
_CRESET1: R8.2, TP19.TP; also elsewhere on the board
_CRESET2: R25.2, TP25.TP; also elsewhere on the board
_CRESET3: R19.2, TP31.TP; also elsewhere on the board
_CS0: R12.1, TP9.TP; also elsewhere on the board
_CS2: R24.1, TP21.TP; also elsewhere on the board
_CS3: R18.1, TP27.TP; also elsewhere on the board
_CS4: R7.1, TP15.TP; also elsewhere on the board
_MISO0: MOTOR0.7, R9.1, R10.2, TP12.TP; also elsewhere on the board
_MISO3: MOTOR3.7, R15.1, R16.2, TP30.TP; also elsewhere on the board
_MISO4: MOTOR1.7, R4.1, R5.2, TP18.TP; also elsewhere on the board
_MISO6: MOTOR2.7, R21.1, R22.2, TP24.TP
_MOSI0: R2.1, TP11.TP; also elsewhere on the board
_MOSI3: R14.1, TP29.TP; also elsewhere on the board
_MOSI4: R1.1, TP17.TP; also elsewhere on the board
_MOSI6: R20.1, TP23.TP; also elsewhere on the board
